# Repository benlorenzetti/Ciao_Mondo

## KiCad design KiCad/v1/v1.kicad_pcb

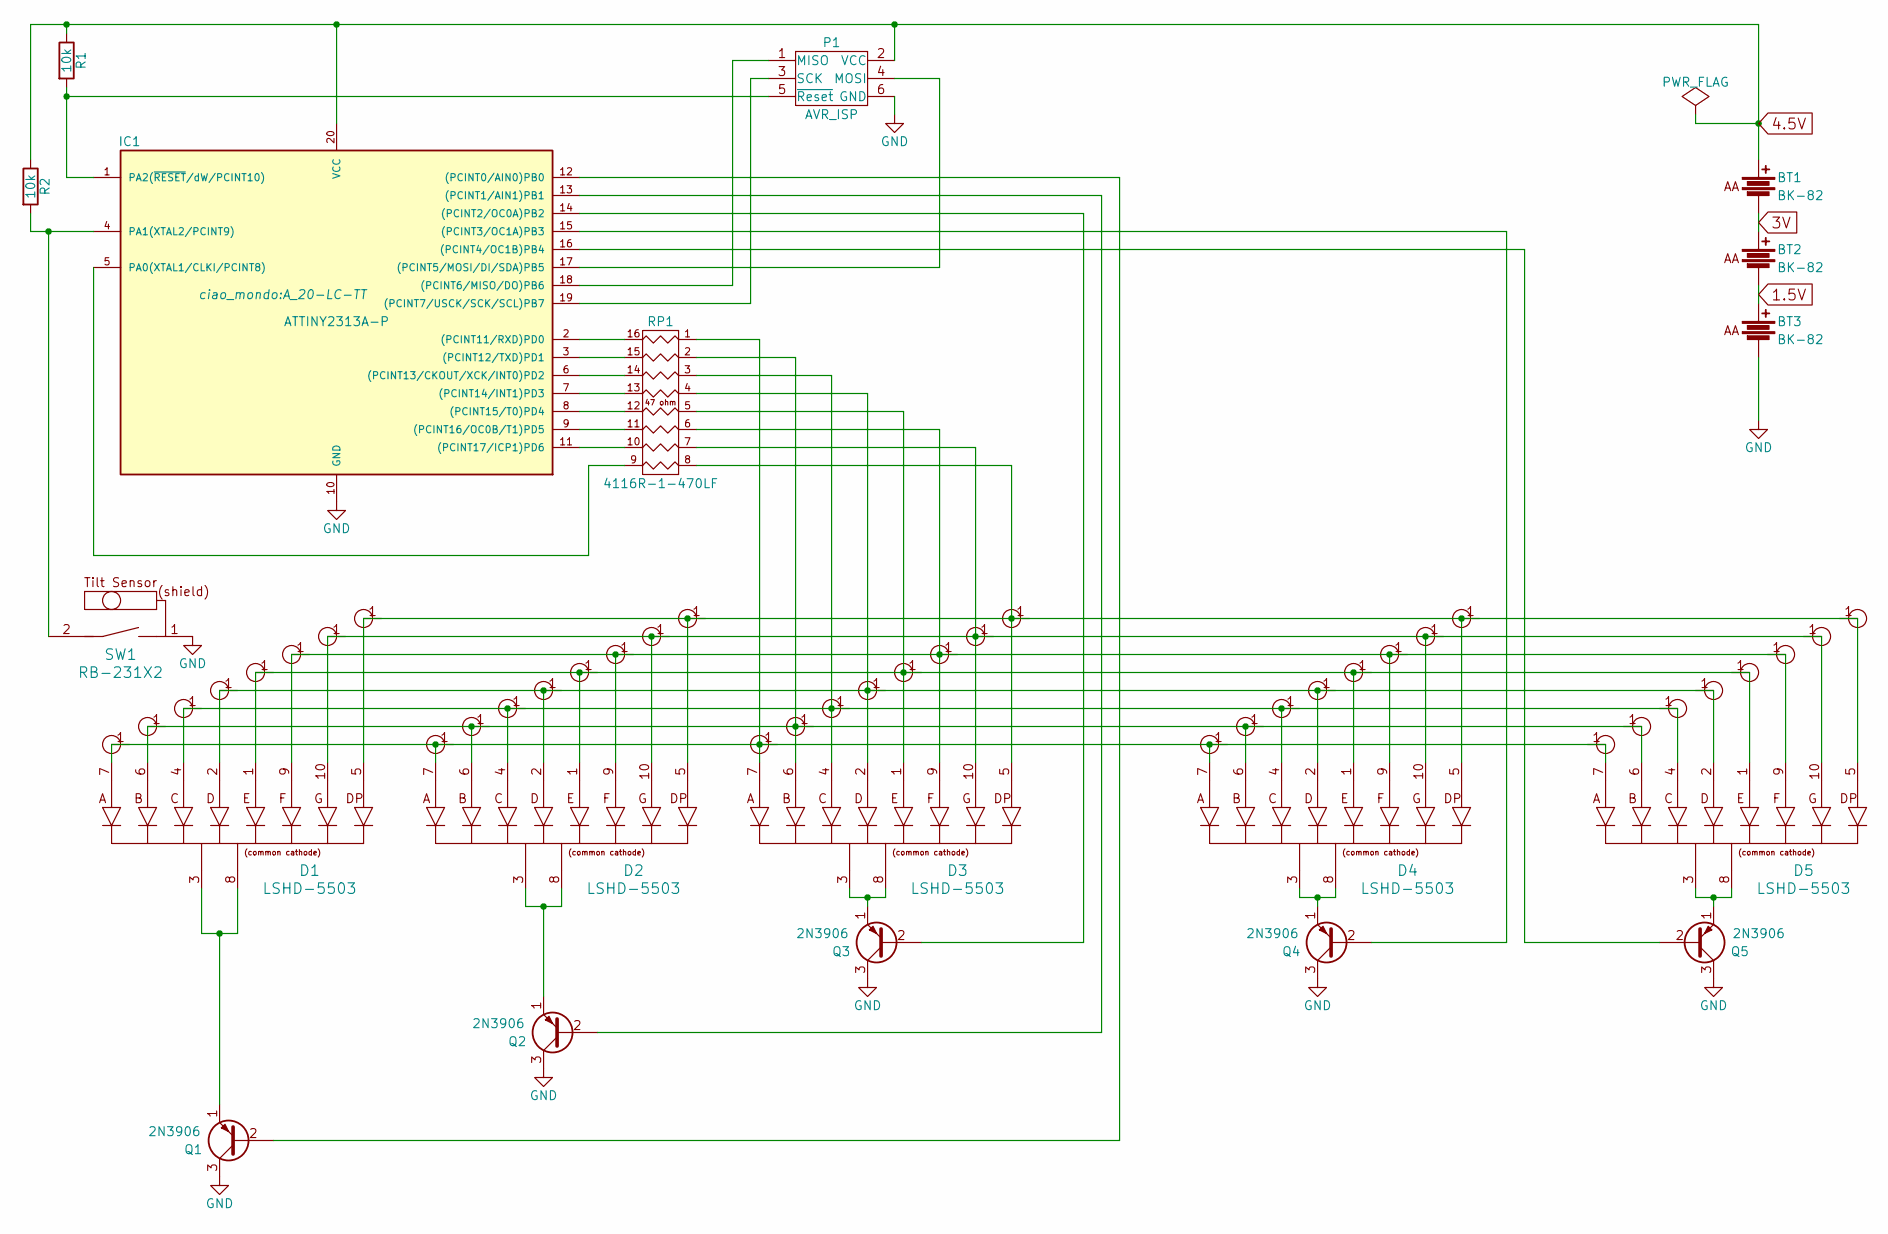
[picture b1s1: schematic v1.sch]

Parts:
BT1, BT2, BT3: BK-82
D1, D2, D3, D4, D5: LSHD-5503
IC1: ATTINY2313A-P; A_20-LC-TT
P1: AVR_ISP; 67997-206HLF
Q1, Q2, Q3, Q4, Q5: 2N3906; TO-92
R1, R2: 10k; Resistor_Horizontal_RM10mm
RP1: 4116R-1-470LF; 4816-3000-CP
SW1: RB-231X2
U1, U2, U3, U4, U5, U6, U7, U8, U9, U10, U11, U12, U13, U14, U15, U16, U17, U18, U19, U20, U21, U22, U23, U24, U25, U26, U27, U28, U29, U30, U31, U32, U33, U34, U35, U36, U37, U38, U39, U40: via

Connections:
1.5V: BT2.2, BT3.1
3V: BT1.2, BT2.1
4.5V: BT1.1, IC1.20 (VCC), P1.2 (VCC), R1.1, R2.1
GND: BT3.2, IC1.10 (GND), P1.6 (GND), Q1.3 (C), Q2.3 (C), Q3.3 (C), Q4.3 (C), Q5.3 (C), SW1.1
unnamed: D1.1, D2.1, D3.1, D4.1, D5.1, RP1.5, U5.1, U13.1, U21.1, U29.1, U37.1
unnamed: D1.2, D2.2, D3.2, D4.2, D5.2, RP1.4, U4.1, U12.1, U20.1, U28.1, U36.1
unnamed: D1.3, D1.8, Q1.1 (E)
unnamed: D1.4, D2.4, D3.4, D4.4, D5.4, RP1.3, U3.1, U11.1, U19.1, U27.1, U35.1
unnamed: D1.5, D2.5, D3.5, D4.5, D5.5, RP1.8, U8.1, U16.1, U24.1, U32.1, U40.1
unnamed: D1.6, D2.6, D3.6, D4.6, D5.6, RP1.2, U2.1, U10.1, U18.1, U26.1, U34.1
unnamed: D1.7, D2.7, D3.7, D4.7, D5.7, RP1.1, U1.1, U9.1, U17.1, U25.1, U33.1
unnamed: D1.9, D2.9, D3.9, D4.9, D5.9, RP1.6, U6.1, U14.1, U22.1, U30.1, U38.1
unnamed: D1.10, D2.10, D3.10, D4.10, D5.10, RP1.7, U7.1, U15.1, U23.1, U31.1, U39.1
unnamed: D2.3, D2.8, Q2.1 (E)
unnamed: D3.3, D3.8, Q3.1 (E)
unnamed: D4.3, D4.8, Q4.1 (E)
unnamed: D5.3, D5.8, Q5.1 (E)
unnamed: IC1.1 (PA2(~RESET~/dW/PCINT10)), P1.5 (~Reset), R1.2
unnamed: IC1.2 ((PCINT11/RXD)PD0), RP1.16 (R1)
unnamed: IC1.3 ((PCINT12/TXD)PD1), RP1.15 (R2)
unnamed: IC1.4 (PA1(XTAL2/PCINT9)), R2.2, SW1.2
unnamed: IC1.5 (PA0(XTAL1/CLKI/PCINT8)), RP1.9 (R8)
unnamed: IC1.6 ((PCINT13/CKOUT/XCK/INT0)PD2), RP1.14 (R3)
unnamed: IC1.7 ((PCINT14/INT1)PD3), RP1.13 (R4)
unnamed: IC1.8 ((PCINT15/T0)PD4), RP1.12 (R5)
unnamed: IC1.9 ((PCINT16/OC0B/T1)PD5), RP1.11 (R6)
unnamed: IC1.11 ((PCINT17/ICP1)PD6), RP1.10 (R7)
unnamed: IC1.12 ((PCINT0/AIN0)PB0), Q1.2 (B)
unnamed: IC1.13 ((PCINT1/AIN1)PB1), Q2.2 (B)
unnamed: IC1.14 ((PCINT2/OC0A)PB2), Q3.2 (B)
unnamed: IC1.15 ((PCINT3/OC1A)PB3), Q4.2 (B)
unnamed: IC1.16 ((PCINT4/OC1B)PB4), Q5.2 (B)
unnamed: IC1.17 ((PCINT5/MOSI/DI/SDA)PB5), P1.4 (MOSI)
unnamed: IC1.18 ((PCINT6/MISO/DO)PB6), P1.1 (MISO)
unnamed: IC1.19 ((PCINT7/USCK/SCK/SCL)PB7), P1.3 (SCK)

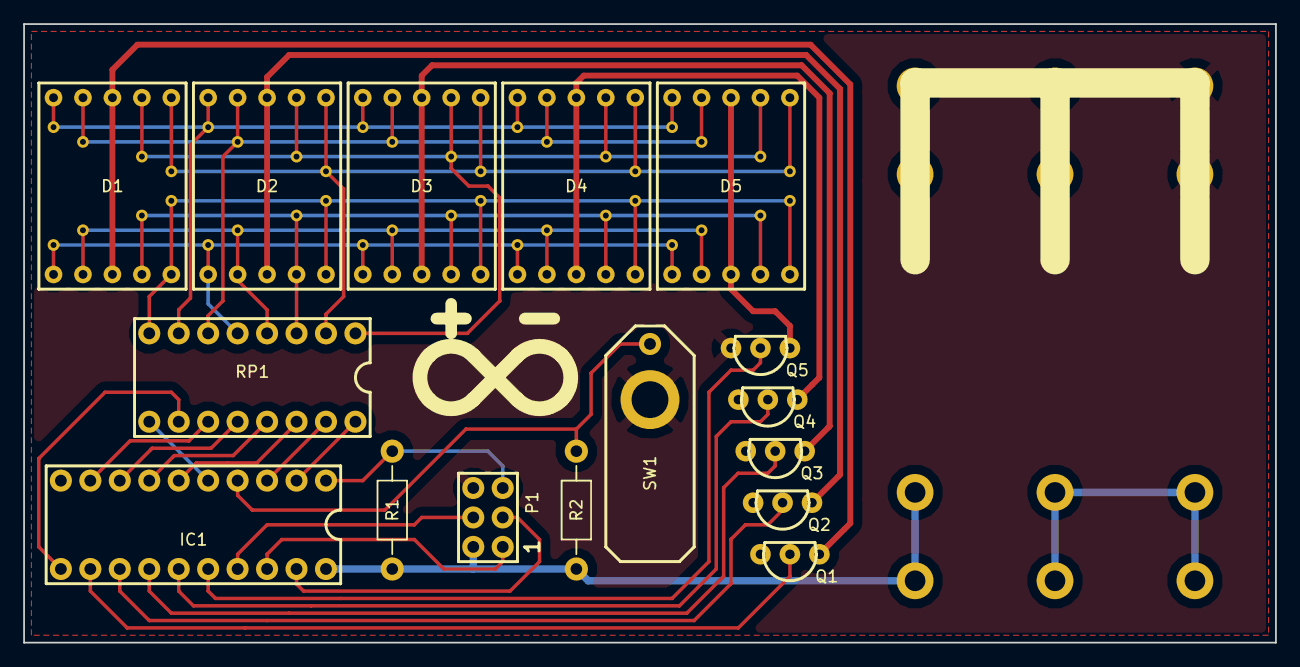
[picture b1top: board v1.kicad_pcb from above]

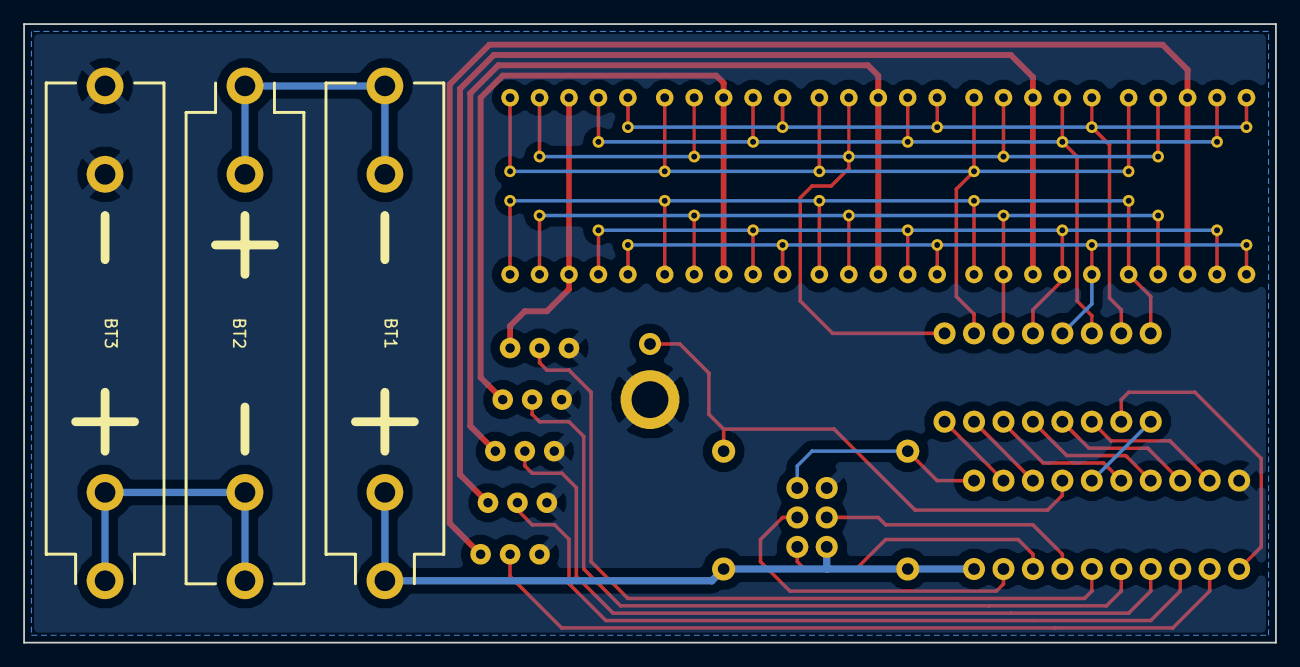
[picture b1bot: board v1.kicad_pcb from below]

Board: 2 copper layers, 107.9 x 53.3 mm, 59 parts (3 on the bottom side), 35 nets.

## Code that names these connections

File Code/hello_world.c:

/* hello_world.c */

/* Is this Board 1 or 2? */
#define BOARD 2

/* Define IO Pins */
#define DIG0 PB0
#define DIG1 PB1
#define DIG2 PB2
#define DIG3 PB3
#define DIG4 PB4

#define SEGA PD0
#define SEGB PD1
#define SEGC PD2
#define SEGD PD3
#define SEGE PD4
#define SEGF PD5
#define SEGG PD6
#define SEGDP PA0

#define TILT PA1

/* Define Polarity of Various IO Signals */
#define SEG_ON 1
#define DIG_ON 0  /* pull the digit's common-cathode to ground */
#define ENGLISH 0
#define ITALIAN 1

/* Just to Make Things More Convoluted */
#define HIGH 1
#define LOW 0
#define COMMON_TONGUE ENGLISH
#define VALERIAN ITALIAN

#include <string.h>
#include <avr/io.h>

const char en_H = 1 << SEGF | 1 << SEGE | 1 << SEGG | 1 << SEGB | 1 << SEGC;
const char en_E = 1 << SEGB | 1 << SEGC | 1 << SEGA | 1 << SEGG | 1 << SEGD;
const char en_L = 1 << SEGB | 1 << SEGC | 1 << SEGA;
const char en_O = ~(1 << SEGG);
const char en_o = 1 << SEGA | 1 << SEGF | 1 << SEGB;
const char en_r = 1 << SEGB;
const char en_l = 1 << SEGB | 1 << SEGC;
const char en_d = 1 << SEGA | 1 << SEGB | 1 << SEGE | 1 << SEGF;
const char en_exclamation = 1 << SEGE | 1 << SEGG;
const char en_decimal = 1 << SEGG;
const char it_C = 1 << SEGA | 1 << SEGF | 1 << SEGE | 1 << SEGD;
const char it_i = 1 << SEGA | 1 << SEGD | 1 << SEGE | 1 << SEGC;
const char it_A = ~(1 << SEGD | 1 << SEGG);
const char it_o = 1 << SEGE | 1 << SEGD | 1 << SEGC | 1 << SEGG;
const char it_n = 1 << SEGE | 1 << SEGG | 1 << SEGC;
const char it_d = 1 << SEGE | 1 << SEGD | 1 << SEGC | 1 << SEGG | 1 << SEGB;
const char it_exclamation = 1 << SEGB;
const char it_decimal = 1 << SEGDP;

const char en_r_portA = 1 << SEGDP;
const char en_d_portA = 1 << SEGDP;
const char it_i_portA = 1 << SEGDP;
const char it_A_portA = 1 << SEGDP;
const char en_o_portA = 1 << SEGDP;


void display_function (const char *, const char *);

int main (void) {
  DDRD = 0x7F; /* Set Port D pins 0, 1, 2, 3, 4, 5, & 6 pins to output */
  DDRB = 0x1F; /* Set Prot B pins 0, 1, 2, 3, & 4 to output */
  DDRA = (1 << SEGDP) | (0 << TILT);
  PORTD = 1 << SEGC;
  PORTB = 0xFE;
  char five_letters[5];
  char punctuations[5];
  for (;;) {
    memset (punctuations, 0, 5);
    /* If board #1 and tilted English, display "HELLO"              */
    if (BOARD == 1 && (PINA & 1<<TILT) == (ENGLISH << TILT) )
    {
      five_letters[4] = en_H;
      five_letters[3] = en_E;
      five_letters[2] = en_L;
      five_letters[1] = en_L;
      five_letters[0] = en_O;
    }
    /* If board #2 and tilted English, display W "orld!"            */
    else if (BOARD == 2 && (PINA & 1<<TILT) == (ENGLISH << TILT))
    {
      five_letters[4] = en_o;
      punctuations[4] = en_o_portA;
      five_letters[3] = en_r;
      punctuations[3] = en_r_portA;
      five_letters[2] = en_l;
      five_letters[1] = en_d;
      punctuations[1] = en_d_portA;
      five_letters[0] = en_exclamation;
      punctuations[0] = en_decimal;
    }
    /* If board #2 and tilted Italian, display "ciao" M             */
    else if (BOARD == 2 && (PINA & 1<<TILT) == (ITALIAN << TILT))
    {
      five_letters[0] = 0;
      five_letters[1] = it_C;
      five_letters[2] = it_i;
      punctuations[2] = it_i_portA;
      five_letters[3] = it_A;
      punctuations[3] = it_A_portA;
      five_letters[4] = en_O;
    }
    /* If board #1 and tilted Italian, display "ondo!"              */
    else
    {
      five_letters[0] = it_o;
      five_letters[1] = it_n;
      five_letters[2] = it_d;
      five_letters[3] = it_o;
      five_letters[4] = it_exclamation;
      punctuations[4] = it_decimal;
    }

    /* Multiplex the 5 letters, timesharing between the 5 displays  */
    display_function (five_letters, punctuations);
  }
  /* This Point Should Never be Reached! */
  return 1;
}

void display_function (const char *letters, const char *decimals)
{
  int time;
  for (time = 0; time < 256; time++)
  {
    if (time < 50) {
      PORTB = ~ (1 << DIG0);
      PORTD = letters[0];
      PORTA = decimals[0];
    }
    else if (time < 100) {
      PORTB = ~ (1 << DIG1);
      PORTD = letters[1];
      PORTA = decimals[1];
    }
    else if (time < 150) {
      PORTB = ~ (1 << DIG2);
      PORTD = letters[2];
      PORTA = decimals[2];
    }
    else if (time < 200) {
      PORTB = ~ (1 << DIG3);
      PORTD = letters[3];
      PORTA = decimals[3];
    }
    else {
      PORTB = ~ (1 << DIG4);
      PORTD = letters[4];
      PORTA = decimals[4];
    }
  }
  return;
}

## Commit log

2016-04-16 PCB Created
2016-05-04 Board Soldered and Programming/LEDs Working
2016-05-04 code mostly complete
2016-05-04 Code Complete for Italy, need to change 4 Display orientations before publishing
